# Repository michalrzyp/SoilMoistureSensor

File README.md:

# SoilMoistureSensor
The assumption of the project was to create a soil moisture sensor and a station collecting measurement results, 
which by analyzing the received data provides information on the degree of soil moisture. 
The sensor placed in the pot sends information via radio to the base station, which is located anywhere in the apartment / house. 
The sensor measured humidity by measuring its resistance.

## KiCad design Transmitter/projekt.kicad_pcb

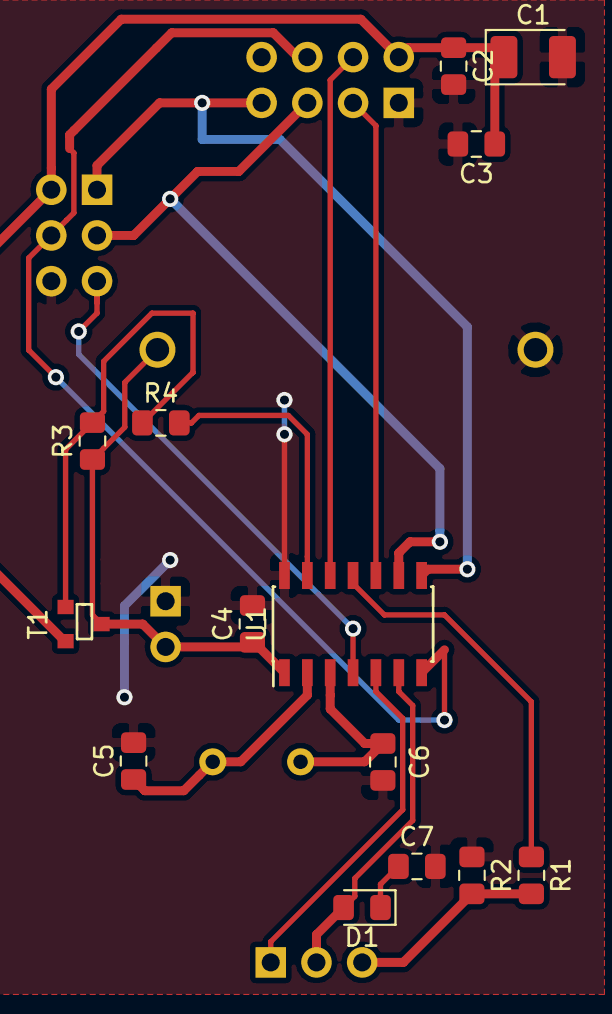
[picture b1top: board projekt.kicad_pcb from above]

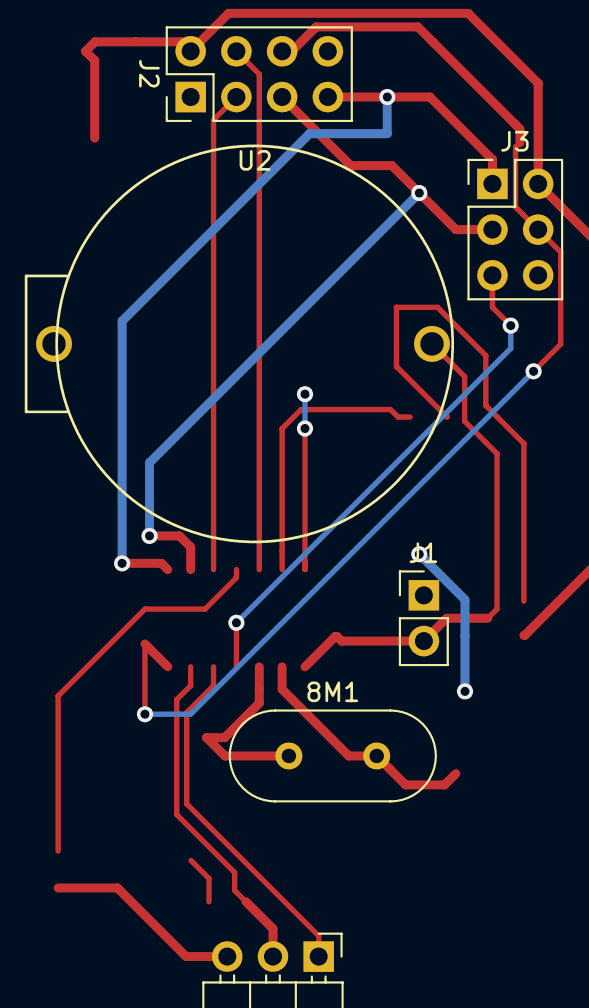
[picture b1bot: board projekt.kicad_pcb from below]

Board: 2 copper layers, 20 parts (6 on the bottom side), 18 nets.

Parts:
8M1: Crystal_Small; Crystal_HC49-4H_Vertical
C1: 100u; CP_EIA-3528-21_Kemet-B_Pad1.50x2.35mm_HandSolder
C2, C3, C4: 100n; C_0805_2012Metric_Pad1.15x1.40mm_HandSolder
C5, C6, C7: 22p; C_0805_2012Metric_Pad1.15x1.40mm_HandSolder
D1: 1N4148; D_0805_2012Metric_Pad1.15x1.40mm_HandSolder
J1: Conn_01x02; PinHeader_1x02_P2.54mm_Vertical
J2: Conn_02x04_Odd_Even; PinHeader_2x04_P2.54mm_Vertical
J3: AVR-ISP-6; PinHeader_2x03_P2.54mm_Vertical
J4: Conn_01x03; PinHeader_1x03_P2.54mm_Horizontal
R1, R2: 0; R_0805_2012Metric_Pad1.15x1.40mm_HandSolder
R3, R4: R_Small; R_0805_2012Metric_Pad1.15x1.40mm_HandSolder
T1: DMG2305UX; moj
U1: ATtiny84A-SSU; SOIC-14_3.9x8.7mm_P1.27mm
U2: DS1092-04-B6P

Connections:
+3V3: C4.1, J1.2, R3.1, T1.3, U1.1, U2.2
/CE: J2.3, U1.10
/CSN: J2.4, U1.12
/GEN: J4.1, U1.5
/MISO: J2.7, J3.1, U1.8
/MOSI: J2.6, J3.4, U1.7
/SCK: J2.5, J3.3, U1.9
/VCC_R: C1.1, C2.1, C3.1, J2.2, J3.2, T1.2
/ZAS_RADIO: R4.2, U1.13
/czujnik: D1.2, J4.2, U1.6
/pinHL: R1.1, U1.11
/~RESET: J3.5, U1.4
GND: C1.2, C2.2, C3.2, C4.2, C5.2, C6.2, C7.2, J1.1, J2.1, J3.6, R2.1, U1.14, U2.1
unnamed: 8M1.1, C6.1, U1.3
unnamed: 8M1.2, C5.1, U1.2
unnamed: C7.1, D1.1
unnamed: J4.3, R1.2, R2.2
unnamed: R3.2, R4.1, T1.1

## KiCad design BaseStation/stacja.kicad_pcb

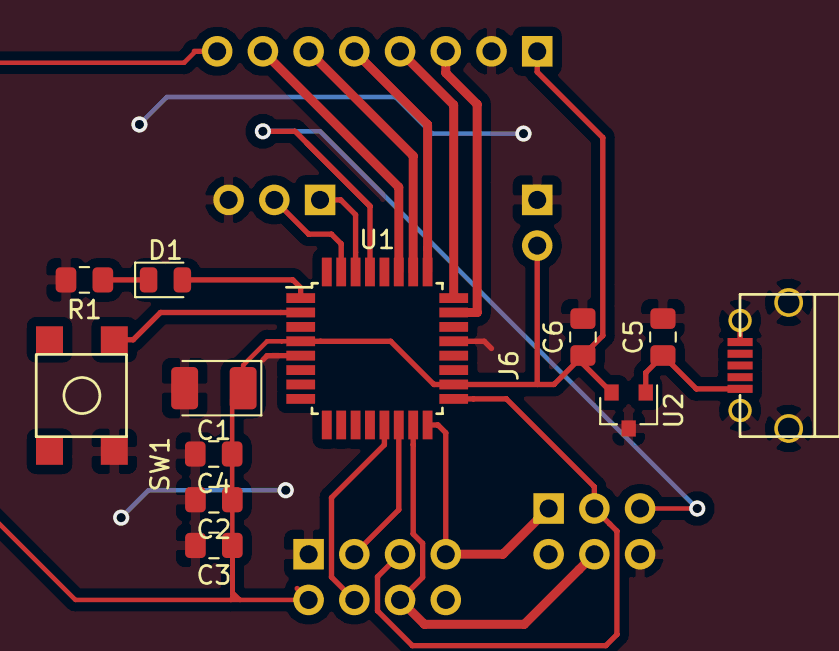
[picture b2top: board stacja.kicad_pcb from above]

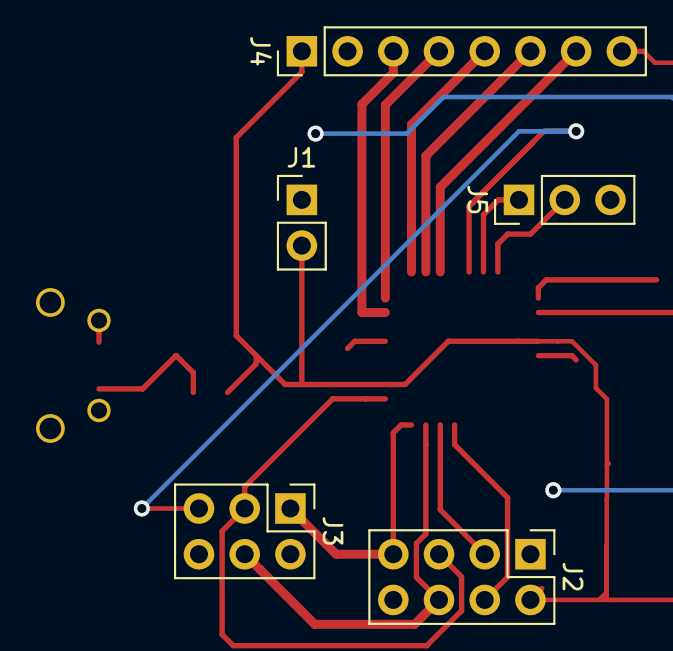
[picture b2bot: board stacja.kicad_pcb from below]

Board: 2 copper layers, 17 parts (5 on the bottom side), 19 nets.

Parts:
C1: 100u; CP_EIA-3528-21_Kemet-B_Pad1.50x2.35mm_HandSolder
C2, C3, C4: 100n; C_0805_2012Metric_Pad1.15x1.40mm_HandSolder
C5, C6: 1u; C_0805_2012Metric_Pad1.15x1.40mm_HandSolder
D1: LED_Small; LED_0805_2012Metric
J1: Conn_01x02; PinHeader_1x02_P2.54mm_Vertical
J2: Conn_02x04_Odd_Even; PinHeader_2x04_P2.54mm_Vertical
J3: AVR-ISP-6; PinHeader_2x03_P2.54mm_Vertical
J4: Conn_01x08; PinHeader_1x08_P2.54mm_Vertical
J5: Conn_01x03; PinHeader_1x03_P2.54mm_Vertical
J6: USB_B_Micro; microusb
R1: 1k; R_0805_2012Metric_Pad1.15x1.40mm_HandSolder
SW1: SW_Push; button
U1: ATmega328PB-AU; TQFP-32_7x7mm_P0.8mm
U2: AP7333; SOT-23

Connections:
+3V3: C1.1, C2.1, C3.1, C4.1, C6.1, J1.2, J2.2, J4.1, J4.8, U1.4, U1.18, U2.2
/BUTTON1: SW1.1, U1.2
/CE: J2.3, U1.14
/CSN: J2.4, U1.13
/LCD_A0: J4.5, U1.25
/LCD_CS: J4.3, U1.23
/LCD_MOSI: J4.6, U1.26
/LCD_RST: J4.4, U1.24
/LCD_SCK: J4.7, U1.27
/LED: D1.2, U1.1
/MISO: J2.7, J3.1, U1.16
/MOSI: J2.6, J3.4, U1.15
/RX: J5.1, U1.30
/SCK: J2.5, J3.3, U1.17
/TX: J5.2, U1.31
/~RESET: J3.5, U1.29
GND: C1.2, C2.2, C3.2, C4.2, C5.2, C6.2, J1.1, J2.1, J3.6, J4.2, J5.3, J6.5, J6.6, R1.2, SW1.2, U1.5, U1.21, U2.3
unnamed: C5.1, J6.1, U2.1
unnamed: D1.1, R1.1
